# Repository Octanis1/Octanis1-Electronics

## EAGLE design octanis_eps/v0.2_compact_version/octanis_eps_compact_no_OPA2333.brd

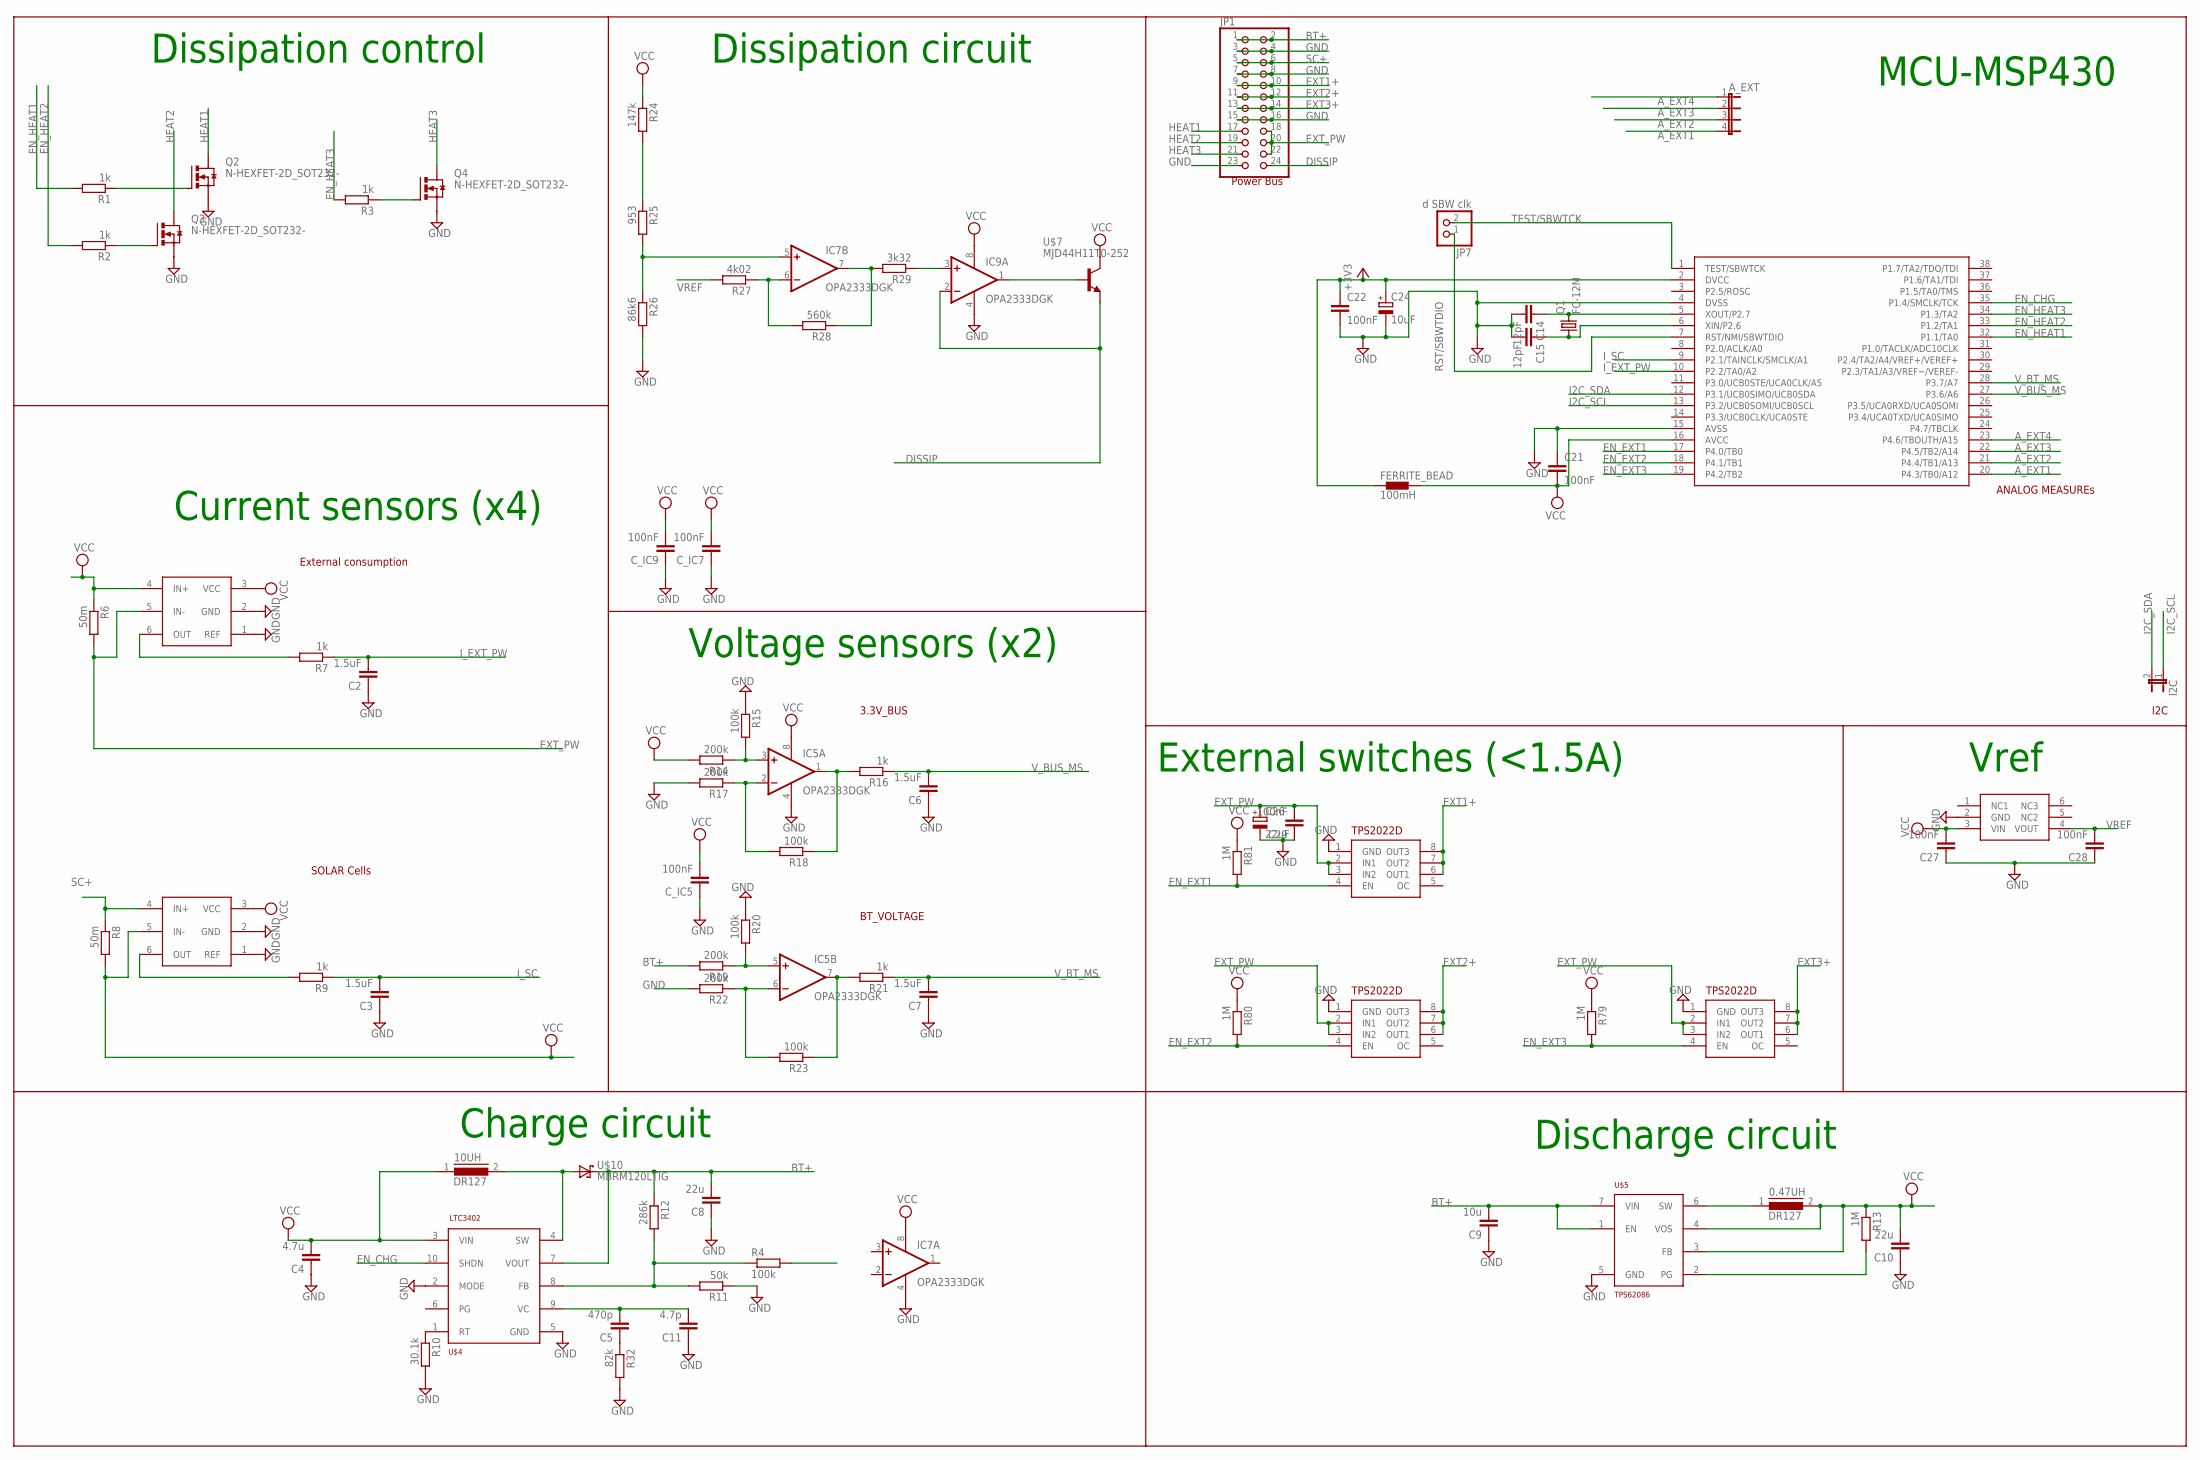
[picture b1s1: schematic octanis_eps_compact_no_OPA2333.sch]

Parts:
0.47UH, 10UH: DR127
A_EXT: JP4E; JP4
C2, C3, C6, C7: 1.5uF; C0603
C4: 4.7u; C1206
C5: 470p; C0603
C8: 22u; C0603
C9: 10u; C1206
C10: 22u; C1206
C11: 4.7p; C0603
C14, C15: 12pF; C0603
C21, C22, C27, C28, C29: 100nF; C0603
C24: 10uF; A/3216-18R
C26: 22uF; A/3216-18R
C_IC5, C_IC7, C_IC9: 100nF; C0603
FERRITE_BEAD: 100mH; 0402
I2C: JP1E; JP1
IC5, IC7, IC9: OPA2333DGK; MSOP08
JP1: PINHD-2X12; 2X12
JP7: d SBW clk; 1X02
Q1: FC-12M
Q2, Q3, Q4: N-HEXFET-2D_SOT232-; SOT223
R1, R2, R3, R7, R9, R16, R21: 1k; R0603
R4, R15, R18, R20, R23: 100k; R0603
R6, R8: 50m; R1206
R10: 30.1k; R0603
R11: 50k; R0603
R12: 286k; R0603
R13, R79, R80, R81: 1M; R0603
R14, R17, R19, R22: 200k; R0603
R24: 147k; R0603
R25: 953; R0603
R26: 86k6; R0603
R27: 4k02; R0603
R28: 560k; R0603
R29: 3k32; R0603
R32: 82k; R0603
U$2, U$3: INA213; SC70-6
U$4: LTC3402; MSOP10
U$5: TPS62086; QFN-7
U$6: MSP430G2544; TSSOP38
U$7: MJD44H11T0-252; TO252
U$10: MBRM120LTIG; DO216AA
U$16, U$17, U$18: TPS2022D; SO8
U$19: ADR127B; TSOT23-6

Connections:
+3V3: C22.1, C24.+, FERRITE_BEAD.1, U$6.2 (DVCC)
A_EXT1: A_EXT.4, U$6.20 (P4.3/TB0/A12)
A_EXT2: A_EXT.3, U$6.21 (P4.4/TB1/A13)
A_EXT3: A_EXT.2, U$6.22 (P4.5/TB2/A14)
A_EXT4: A_EXT.1, U$6.23 (P4.6/TBOUTH/A15)
BT+: C8.2, C9.2, JP1.1, JP1.2, R12.1, R19.2, U$4.7 (VOUT), U$5.1 (EN), U$5.7 (VIN), U$10.C (K)
DISSIP: IC9.2 (-IN), JP1.24, U$7.3 (E)
EN_CHG: U$4.10 (SHDN), U$6.35 (P1.4/SMCLK/TCK)
EN_EXT1: R81.2, U$6.17 (P4.0/TB0), U$16.4 (EN)
EN_EXT2: R80.2, U$6.18 (P4.1/TB1), U$17.4 (EN)
EN_EXT3: R79.2, U$6.19 (P4.2/TB2), U$18.4 (EN)
EN_HEAT1: R1.2, U$6.32 (P1.1/TA0)
EN_HEAT2: R2.2, U$6.33 (P1.2/TA1)
EN_HEAT3: R3.2, U$6.34 (P1.3/TA2)
EXT1+: JP1.9, JP1.10, U$16.6 (OUT1), U$16.7 (OUT2), U$16.8 (OUT3)
EXT2+: JP1.11, JP1.12, U$17.6 (OUT1), U$17.7 (OUT2), U$17.8 (OUT3)
EXT3+: JP1.13, JP1.14, U$18.6 (OUT1), U$18.7 (OUT2), U$18.8 (OUT3)
EXT_PW: C26.+, C29.2, JP1.18, JP1.20, JP1.22, R6.2, U$2.5 (IN-), U$16.2 (IN1), U$16.3 (IN2), U$17.2 (IN1), U$17.3 (IN2), U$18.2 (IN1), U$18.3 (IN2)
GND: C2.1, C3.1, C4.1, C6.1, C7.1, C8.1, C9.1, C10.1, C11.1, C14.2, C15.2, C21.1, C22.2, C24.-, C26.-, C27.1, C28.1, C29.1, C_IC5.1, C_IC7.1, C_IC9.1, IC5.4 (V-), IC7.4 (V-), IC9.4 (V-), JP1.3, JP1.4, JP1.7, JP1.8, JP1.15, JP1.16, JP1.23, Q2.3 (S), Q3.3 (S), Q4.3 (S), R10.2, R11.1, R15.1, R17.2, R20.1, R22.2, R26.2, R32.2, U$2.1 (REF), U$2.2 (GND), U$3.1 (REF), U$3.2 (GND), U$4.2 (MODE), U$4.5 (GND), U$5.5 (GND), U$6.4 (DVSS), U$6.15 (AVSS), U$16.1 (GND), U$17.1 (GND), U$18.1 (GND), U$19.2 (GND)
HEAT1: JP1.17, Q2.2 (D), Q2.4 (D)
HEAT2: JP1.19, Q3.2 (D), Q3.4 (D)
HEAT3: JP1.21, Q4.2 (D), Q4.4 (D)
I2C_SCL: I2C.1, U$6.13 (P3.2/UCB0SOMI/UCB0SCL)
I2C_SDA: I2C.2, U$6.12 (P3.1/UCB0SIMO/UCB0SDA)
I_EXT_PW: C2.2, R7.1, U$6.10 (P2.2/TA0/A2)
I_SC: C3.2, R9.1, U$6.9 (P2.1/TAINCLK/SMCLK/A1)
unnamed: R7.2, U$2.6 (OUT)
unnamed: R9.2, U$3.6 (OUT)
unnamed: R10.1, U$4.1 (RT)
unnamed: C5.1, R32.1
unnamed: C5.2, C11.2, U$4.9 (VC)
unnamed: IC5.7 (OUT), R21.2, R23.1
unnamed: IC5.1 (OUT), R16.2, R18.1
unnamed: IC5.2 (-IN), R17.1, R18.2
unnamed: IC5.3 (+IN), R14.1, R15.2
unnamed: IC5.6 (-IN), R22.1, R23.2
unnamed: IC5.5 (+IN), R19.1, R20.2
unnamed: R24.2, R25.1
unnamed: IC7.5 (+IN), R25.2, R26.1
unnamed: IC7.6 (-IN), R27.1, R28.2
unnamed: IC7.7 (OUT), R28.1, R29.2
unnamed: IC9.3 (+IN), R29.1
unnamed: R4.1, R11.2, R12.2, U$4.8 (FB)
unnamed: 10UH.2, U$4.4 (SW), U$10.A
unnamed: R13.2, U$5.2 (PG)
unnamed: 0.47UH.1, U$5.6 (SW)
unnamed: Q2.1 (G), R1.1
unnamed: Q3.1 (G), R2.1
unnamed: Q4.1 (G), R3.1
unnamed: IC9.1 (OUT), U$7.1 (B)
unnamed: C14.1, Q1.2, U$6.5 (XOUT/P2.7)
unnamed: C15.1, Q1.1, U$6.6 (XIN/P2.6)
RST/SBWTDIO: JP7.1, U$6.7 (RST/NMI/SBWTDIO)
SC+: JP1.5, JP1.6, R8.1, U$3.4 (IN+)
TEST/SBWTCK: JP7.2, U$6.1 (TEST/SBWTCK)
VCC: 0.47UH.2, 10UH.1, C4.2, C10.2, C21.2, C27.2, C_IC5.2, C_IC7.2, C_IC9.2, FERRITE_BEAD.2, IC5.8 (V+), IC7.8 (V+), IC9.8 (V+), R6.1, R8.2, R13.1, R14.2, R24.1, R79.1, R80.1, R81.1, U$2.3 (VCC), U$2.4 (IN+), U$3.3 (VCC), U$3.5 (IN-), U$4.3 (VIN), U$5.3 (FB), U$5.4 (VOS), U$6.16 (AVCC), U$7.2 (C), U$19.3 (VIN)
VREF: C28.2, R27.2, U$19.4 (VOUT)
V_BT_MS: C7.2, R21.1, U$6.28 (P3.7/A7)
V_BUS_MS: C6.2, R16.1, U$6.27 (P3.6/A6)

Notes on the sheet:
Vref
Current sensors (x4)
SOLAR Cells
3.3V_BUS
Charge circuit
Discharge circuit
External switches (<1.5A)
MCU-MSP430
Voltage sensors (x2)
BT_VOLTAGE
Dissipation circuit
ANALOG MEASUREs
I2C
External consumption
Dissipation control
Power Bus

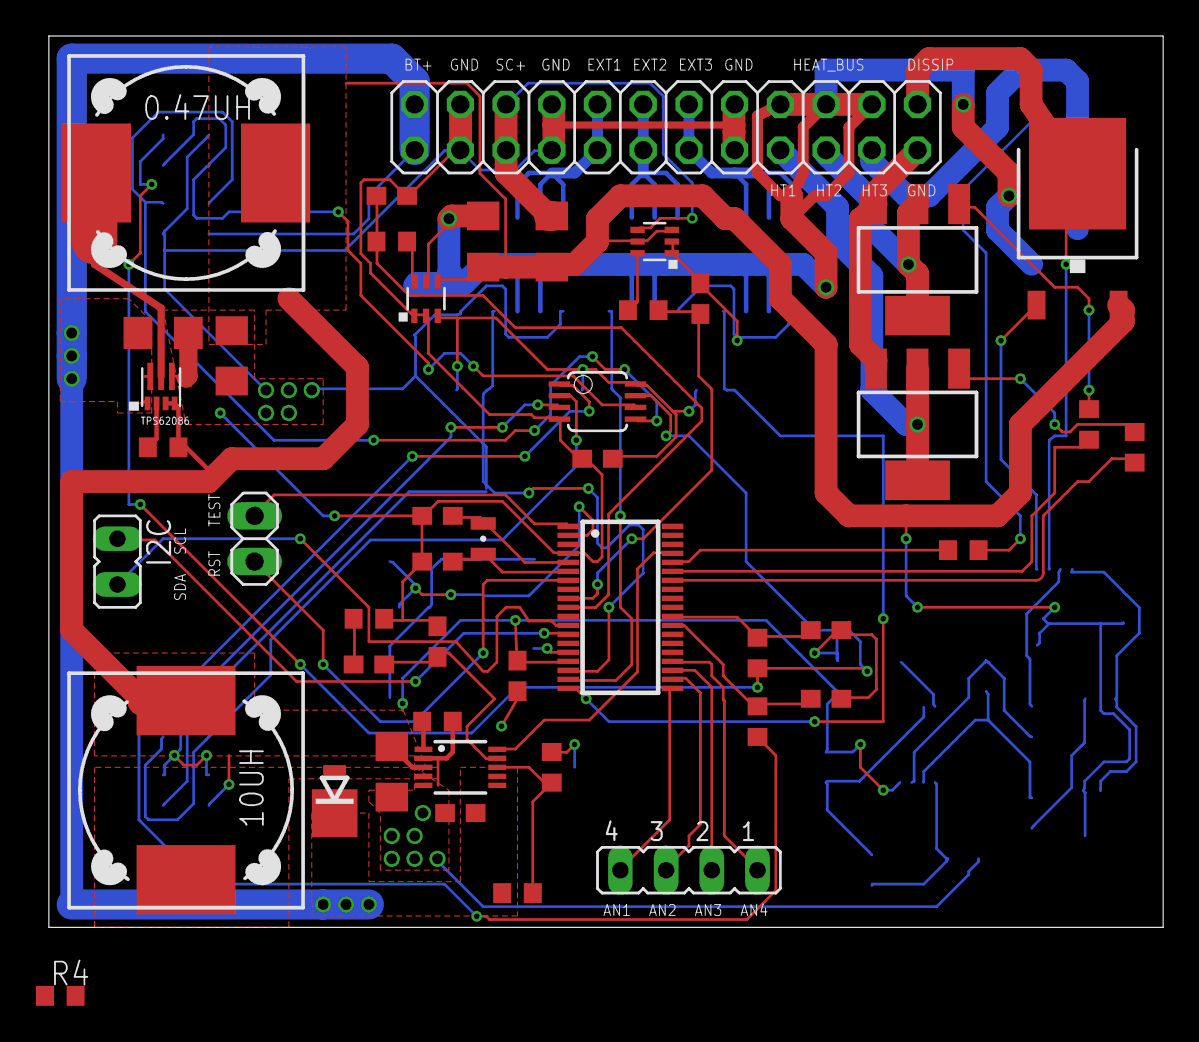
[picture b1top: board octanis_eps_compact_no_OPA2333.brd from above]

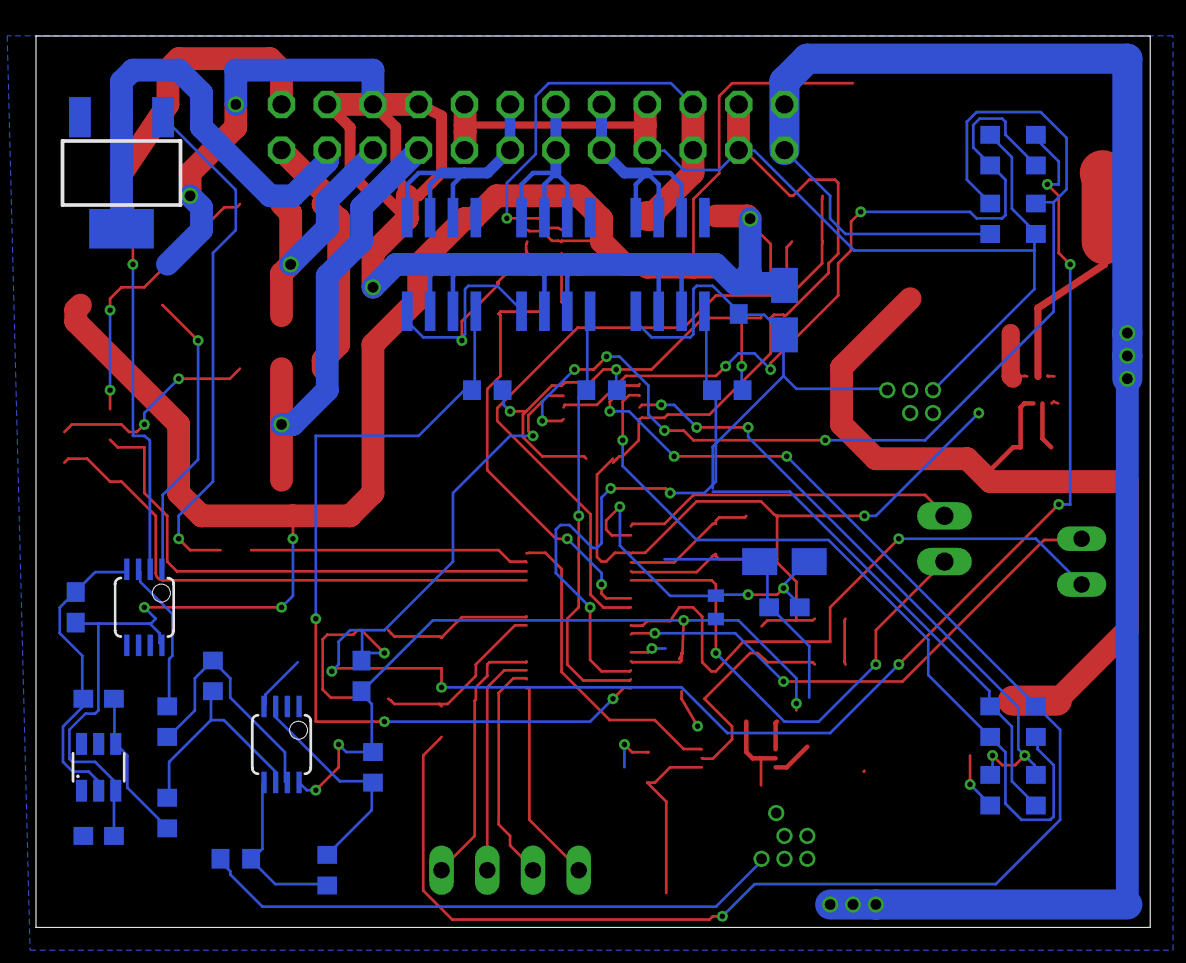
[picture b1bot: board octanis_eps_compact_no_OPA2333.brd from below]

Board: 4 copper layers, 61.9 x 49.5 mm, 79 parts (33 on the bottom side), 59 nets.

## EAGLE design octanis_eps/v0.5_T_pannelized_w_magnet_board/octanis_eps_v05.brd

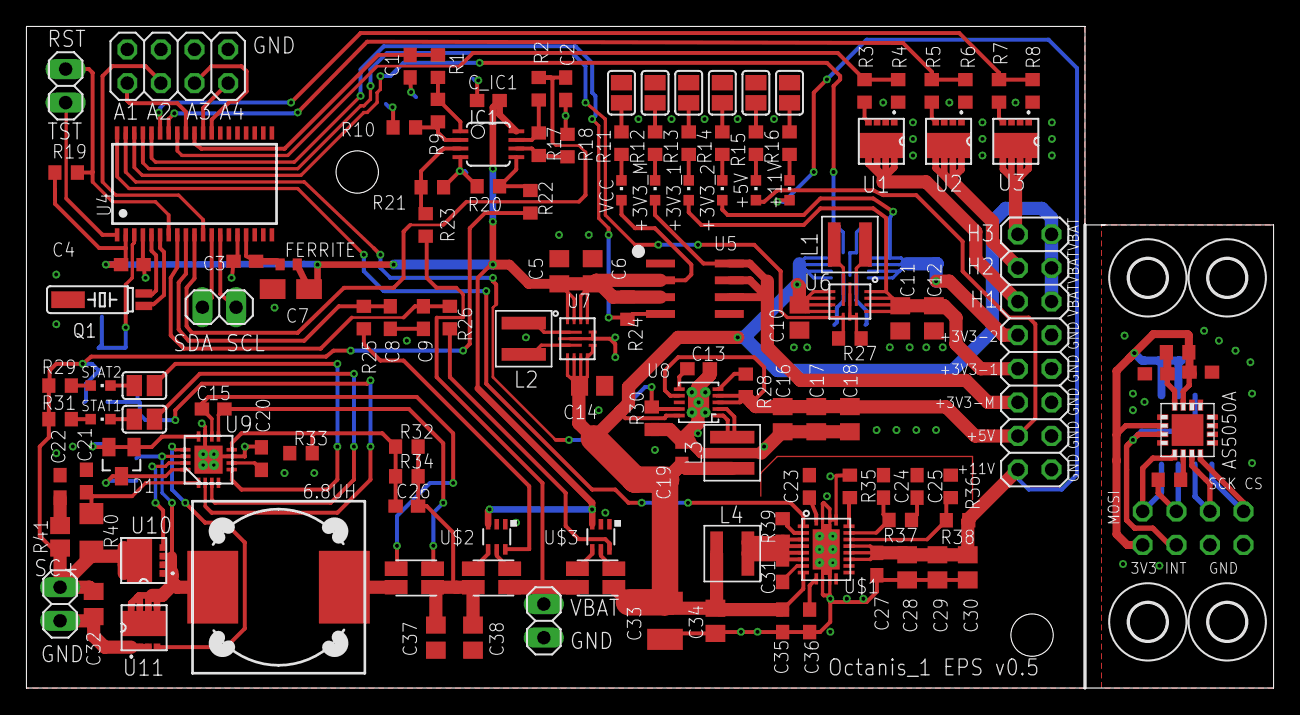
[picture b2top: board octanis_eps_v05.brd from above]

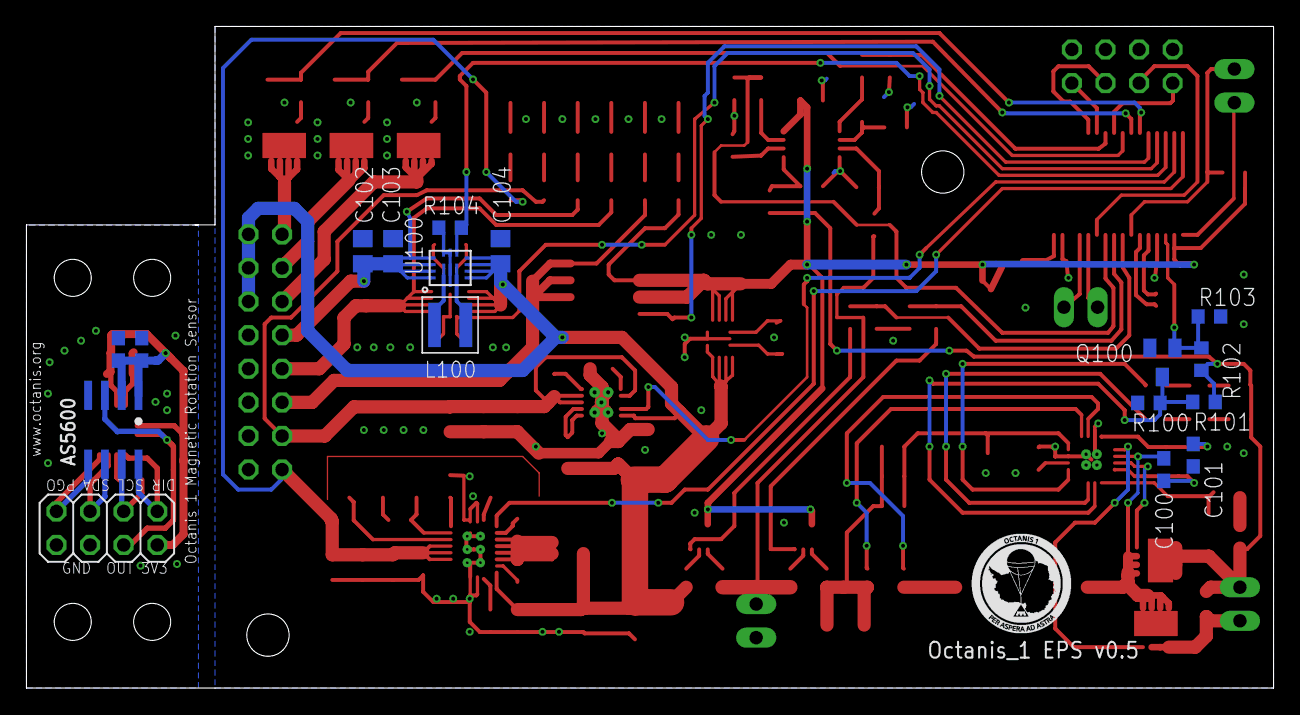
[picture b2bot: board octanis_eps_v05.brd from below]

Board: 2 copper layers, 94.2 x 50.0 mm, 154 parts (17 on the bottom side), 111 nets.

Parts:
6.8UH: DR127
+3V3_1: 3V3-1; CHIPLED_0603
+3V3_2: 3V3-2; CHIPLED_0603
+3V3_M: 3V3-M; CHIPLED_0603
+5V: 5V; CHIPLED_0603
+11V: 12V; CHIPLED_0603
AS5600: AS5600; SOIC-8
C1, C2, C8, C9: 1.5uF; C0603
C3, C4, C15, C31, C35, C100: 100nF; C0603
C5, C6, C11, C12, C16, C17, C18, C28, C29, C30, C102, C103: 22uF; C0805
C7: 10uF; A/3216-18R
C10, C14, C32, C34, C37, C38, C104: 10uF; C0805
C13: 10nF; C0603
C19: 22uF; C0603
C20, C27, C101: 1uF; C0603
C21: 1u; C0603
C22, C23: 2.2uF; C0603
C24: 150pF; C0603
C25: 4.7nF; C0603
C26: 22pF; C0603
C33: 47uF Tantal; C1210
C36: 47nF; C0603
C39: 4u7; C0603
C40, C42: 100n; C0603
C41: 10u; C0603
C_IC1: 100nF; C0603
D1: BAT54C; SOT23
FERRITE: 100mH; 0402
H1, H2, H3, H4: MOUNT-HOLE2.8; 2,8
IC1: OPA2333DGK; MSOP08
J1, J2, J3, J4, J5, J6, J7, J8: SJ
JP1, JP7: 2X04
JP2, JP3, JP5, JP6: 1X02
JP4: 2X08
L1, L2, L3, L100: 1uH; XFL4020
L4: 1.5uH; XFL4020
Q1: 32.768kHz; MS3V-T1R
Q100: BSS123; SOT23
R1, R2, R3, R5, R7, R11, R12, R13, R14, R25, R26: 1k; R0603
R4, R6, R8, R24, R27, R28, R30, R102, R103, R104: 1M; R0603
R9, R17, R20, R21, R32, R33: 100k; R0603
R10, R18, R22, R23: 200k; R0603
R15: 1.5k; R0603
R16: 4.7k; R0603
R19: 10k; R0603
R29, R31: 4k7; R0603
R34: 2.2M; R0603
R35: 270k; R0603
R36: 56k; R0603
R37: 150-220k; R0603
R38: 470k; R0603
R39: 47k; R0603
R40: 10; R1206
R41: 2; R2012
R42, R43: 15R; R0603
R100, R101: R0603
RSENSE1: RSENSE2; 4PADS_RESISTOR
R_SENSE1: RSENSE1 10mOhm; 4PADS_RESISTOR
R_SENSE2: RSENSE1; 4PADS_RESISTOR
STAT1, STAT2: 5V-ok; CHIPLED_0603
U1, U2, U3, U10, U11: CSD16327Q3_DQG_8; DQG8
U4: MSP430G2544; TSSOP38_MSPGXX44_SERIES
U5: TPS2022D; SO8
U6, U7, U100: Value; RNC0014A
U8: TPS61232; S-PVSON-N10
U9: BQ24650_RVA_16; RVA16_2P14X2P14
U$1: TPS61088; R-PVQFN-N20
U$2, U$3: INA213; SC70-6
U$4: AS5050.QFN; QFN.16
VCC: 3V3-EPS; CHIPLED_0603

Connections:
+3V1: AS5600.1, AS5600.2, C40.1, C41.2, C42.2, JP7.2, R42.2, U$4.11, U$4.14
+3V3: C4.1, C5.1, C6.1, C7.+, C_IC1.2, FERRITE.1, IC1.8, R19.2, R24.2, U4.2, U5.2, U5.3, U7.11, U7.12, U7.13, U7.14, U$2.3, U$3.3, VCC.A
+3V3_1: +3V3_1.A, C11.1, C12.1, JP4.8, U6.11, U6.12, U6.13, U6.14
+3V3_2: +3V3_2.A, C102.1, C103.1, JP4.10, U100.11, U100.12, U100.13, U100.14
+3V3_M: +3V3_M.A, JP4.6, U5.6, U5.7, U5.8
+5V: +5V.A, C16.1, C17.1, C18.1, JP4.4, R28.2, U8.3, U8.4, U8.7
+12V: +11V.A, C27.2, C28.2, C29.2, C30.2, JP4.2, R38.2, U$1.P$14, U$1.P$15, U$1.P$16
A_EXT1: JP1.1, U4.30
A_EXT2: JP1.3, U4.11
A_EXT3: JP1.5, U4.27
A_EXT4: JP1.7, U4.28
BAT+: JP6.2, R23.2, RSENSE1.I2, R_SENSE2.I1
BAT_OUT: C10.1, C14.1, C19.1, C33.1, C34.1, C35.1, C104.1, JP4.11, JP4.13, JP4.15, L3.P$1, L4.P$1, R_SENSE2.I2, U6.4, U6.5, U6.6, U6.7, U7.4, U7.5, U7.6, U7.7, U7.8, U8.10, U100.4, U100.5, U100.6, U100.7, U$1.P$9
CS/PGO: AS5600.5, JP7.7, U$4.4
EN_3V3_1: R27.1, U4.35, U6.8
EN_3V3_2: R104.1, U4.36, U100.8
EN_3V3_M: R24.1, U4.34, U5.4
EN_5V: R30.2, U4.37, U8.9
EN_12V: U4.38, U$1.P$2
EN_HEAT1: R3.2, R4.1, U4.31
EN_HEAT2: R5.2, R6.1, U4.32
EN_HEAT3: R7.2, R8.1, U4.33
EN_SC: Q100.1, R102.1, R103.2, U4.3
GND: C1.1, C2.1, C3.2, C4.2, C5.2, C6.2, C7.-, C8.1, C9.1, C10.2, C11.2, C12.2, C13.2, C14.2, C16.2, C17.2, C18.2, C19.2, C20.2, C21.2, C22.2, C23.2, C24.2, C25.2, C27.1, C28.1, C29.1, C30.1, C32.1, C33.2, C34.2, C35.2, C36.2, C37.2, C38.2, C101.2, C102.2, C103.2, C104.2, C_IC1.1, IC1.4, J1.1, J2.1, J3.1, J4.1, J5.1, J6.1, JP1.2, JP1.4, JP1.6, JP1.8, JP4.1, JP4.3, JP4.5, JP4.7, JP4.9, JP5.1, JP6.1, Q1.P3, Q100.2, R4.2, R6.2, R8.2, R10.2, R18.2, R20.1, R21.1, R27.2, R30.1, R33.1, R35.1, R36.1, R100.1, R103.1, R104.2, U1.1, U1.2, U1.3, U2.1, U2.2, U2.3, U3.1, U3.2, U3.3, U4.4, U4.15, U5.1, U6.2, U6.9, U6.10, U7.2, U7.9, U7.10, U8.EXPAD, U8.GND1, U8.GND2, U8.GND3, U8.GND4, U8.GND5, U9.7, U9.11, U9.17, U9.V, U9.V_1, U9.V_2, U9.V_3, U11.1, U11.2, U11.3, U100.2, U100.9, U100.10, U$1.P$20, U$1.PGND1, U$1.PGND2, U$1.PGND3, U$1.PGND4, U$1.PGND5, U$1.PGND6, U$1.PGND7, U$1.PGND8, U$1.PGND9, U$1.PGND10, U$1.PGND11, U$1.PGND12, U$2.1, U$2.2, U$3.1, U$3.2
GND1: AS5600.4, C39.1, C40.2, C41.1, C42.1, JP7.6, JP7.8, U$4.9, U$4.10, U$4.13
HEAT1: JP4.12, U1.5, U1.6, U1.7, U1.8
HEAT2: JP4.14, U2.5, U2.6, U2.7, U2.8
HEAT3: JP4.16, U3.5, U3.6, U3.7, U3.8
I2C_SCL: JP3.2, U4.13
I2C_SDA: JP3.1, U4.12
IND: L3.P$2, U8.1, U8.2
INT/OUT: AS5600.3, JP7.4, U$4.15
I_IN: C8.2, R25.1, U4.9
I_OUT: C9.2, R26.1, U4.8
LED5: +5V.C, R15.2
MISO/SCL: AS5600.7, JP7.3, R43.1
MOSI/DIR: AS5600.8, JP7.1, U$4.1
unnamed: L2.P$1, U7.3
unnamed: R28.1, U8.5
unnamed: L2.P$2, U7.1
unnamed: 6.8UH.2, R_SENSE1.I1
unnamed: C13.1, U8.6
unnamed: L1.P$1, U6.3
unnamed: L1.P$2, U6.1
unnamed: C39.2, R42.1, U$4.12
unnamed: R43.2, U$4.2
unnamed: L100.P$1, U100.3
unnamed: L100.P$2, U100.1
unnamed: J5.2, R15.1
unnamed: IC1.1, R1.2, R9.1
unnamed: IC1.2, R9.2, R10.1
unnamed: IC1.3, R21.2, R23.1
unnamed: IC1.7, R2.2, R17.1
unnamed: IC1.6, R17.2, R18.1
unnamed: IC1.5, R20.2, R22.1
unnamed: R26.2, U$3.6
unnamed: R25.2, U$2.6
unnamed: R7.1, U3.4
unnamed: Q1.P1, U4.6
unnamed: R5.1, U2.4
unnamed: R_SENSE2.V1, U$3.4
unnamed: R_SENSE2.V2, U$3.5
unnamed: RSENSE1.V1, U$2.4
unnamed: RSENSE1.V2, U$2.5
unnamed: Q1.P2, U4.5
unnamed: R3.1, U1.4
unnamed: C31.2, U$1.P$8
unnamed: +3V3_M.C, R12.2
unnamed: J2.2, R12.1
unnamed: R11.2, VCC.C
unnamed: J1.2, R11.1
unnamed: +3V3_2.C, R14.2
unnamed: J4.2, R14.1
unnamed: +11V.C, R16.2
unnamed: J6.2, R16.1
unnamed: C31.1, L4.P$2, R39.2, U$1.P$4, U$1.P$5, U$1.P$6, U$1.P$7
unnamed: +3V3_1.C, R13.2
unnamed: J3.2, R13.1
unnamed: R39.1, U$1.P$3
unnamed: C25.1, R37.1
unnamed: C36.1, U$1.P$10
unnamed: R35.2, U$1.P$19
unnamed: C24.1, R37.2, U$1.P$18
unnamed: C23.1, U$1.P$1
unnamed: R36.2, R38.1, U$1.P$17
unnamed: Q100.3, R100.2, R101.1, U9.2
unnamed: C22.1, R41.1
unnamed: R31.1, STAT1.A
unnamed: J7.2, STAT2.C
unnamed: J8.2, STAT1.C
unnamed: R29.1, STAT2.A
unnamed: J7.1, U9.5
unnamed: J8.1, U9.3
unnamed: C20.1, U9.6
unnamed: C21.1, R40.2, U9.1
unnamed: JP2.2, U4.1
unnamed: 6.8UH.1, C100.1, U9.14, U10.1, U10.2, U10.3, U11.5, U11.6, U11.7, U11.8
unnamed: C15.2, R_SENSE1.V1, U9.10
unnamed: C15.1, R_SENSE1.V2, U9.9
unnamed: U9.15, U10.4
unnamed: U9.13, U11.4
unnamed: C26.2, R32.1, R33.2, R34.1, U9.8
unnamed: C101.1, D1.1, D1.2, U9.12
unnamed: C100.2, D1.3, U9.16
unnamed: JP2.1, R19.1, U4.7
unnamed: C3.1, FERRITE.2, U4.16
SC+: C32.2, JP5.2, R22.2, R29.2, R31.2, R40.1, R41.2, R101.2, R102.2, U10.5, U10.6, U10.7, U10.8
SCLK/SDA: AS5600.6, JP7.5, U$4.3
SC_OUT: C26.1, C37.1, C38.1, R32.2, R34.2, RSENSE1.I1, R_SENSE1.I2
V_BAT: C1.2, R1.1, U4.29
V_SC: C2.2, R2.1, U4.10

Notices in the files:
parts and their libraries:
SparkFun-Sensors: Licensing: CC v3.0 Share-Alike You are welcome to use this library for commercial purposes.
